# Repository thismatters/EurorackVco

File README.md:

# Voltage Controlled Oscillator

A Voltage Contolled Oscillator (VCO) is the backbone module for subtractive synthesis. It generates an audio signal which can then be shaped by myriad filters and amplifiers. Without a VCO you don't have a synth.

The circuit here is based on the [Yusynth VCO](https://yusynth.net/Modular/EN/VCO/index.html) with minor tweaks to make it more Eurorack friendly. The changes I've made are thus:
* Selected resistors appropriate for +/-12V rails,
* Added polarity protection so that a backward power header doesn't fry anything (twin series schotty diodes: BAT54SL),
* Selected a modern dual NPN diode package for the exponential converter,
* Full surface mount design,
* Toggle switch on front face for sync hardness.

The Yusynth page is a treasure trove of information about this circuit that I am too amateur to claim as my own; please read that outstanding page before using this circuit. The page provides several other implementations of the circuit that you may find suitable.

The KiCAD project here uses the library/footprints [found in my companion repo](https://github.com/thismatters/EurorackKiCAD).

## Width

10hp on a standard 3U rack.

## Inputs

This VCO features dual inputs for 1V/oct, Linear FM, and Exponential FM, Sync, and PWM. A toggle switch on the front face allows the player to set sync hardness. Two potentiometers allow the setting of frequency offset: coarse and fine. Two potentiometers are devoted to level for each of the frequency modulators (linear and exponential). Another pair of potentiometers gives control over (inherent) pulse width and PWM input level.

## Outputs

Four wave shapes are simultaneously available:
* Sine
* Triangle
* Saw (falling)
* Square

## Fiddly bits

Three 100kOhm resistors (R3, R4, R5) should be selected to within 0.1% tolerance (of each other) for good input tracking.

Likewise, two diodes (D5 and D6) ought to be selected which have a closely matched bias voltage in order to ensure a good sine wave symmetry. Testing SMD diodes for bias voltage is no small feat, so I didn't really bother doing this on my test circuits and first printed boards and they seemed fine. I hasten to bet that manufacturing processes have improved to the extent that manual matching is no longer relevant; but that could also just be a justification for laziness!

The schematic shows an OPA2134, however the original circuit calls for an OPA2137. The OPA2134 is a higher quality chip for sound applications, but it is also more expensive and was out of stock when I went to order; the OPA2137 is a suitable alternative.

The schematic calls for a `thermally_coupled_transistor_pair`; this is actually two components arranged carefully together. First a dual NPN transistor array (BCM847), then a thermco resistor which is nestled directly atop the transistor array package and the couple are blanketed in thermal grease so that the two components stay close to the same temperature.

## Adjustment

You'll need an oscilloscope, a CV keyboard, and ideally a tuner.

### Waveshape

1. Set the frequency potentiometers to their middle positions, set the FM and PWM level knobs to minimum (counterclockwise), and the PW knob to the middle position.
1. Connect the sawtooth output to the oscilloscope.
1. Power on the circuit.
1. Adjust RV10 until the sawtooth fills the full covers 10V from peak to peak (no horizontal line at top or bottom).
1. Adjust RV9 until the sawtooth is centered about 0V. (You may have to revisit RV10 to get this perfect; before moving on the saw wave should fill the +/-5V range)
1. Connect the triangle output to the oscilloscope.
1. Adjust RV9 some more to get the triangle shape just right.
1. Adjust RV11 until the triangle is centered around 0V. (You may have to revisit RV10 to get this perfect)
1. Connect the sine output to the oscilloscope.
1. The sine wave ought to look about right, but you may adjust RV9, RV11 (and possibly RV10) to hone this.

### Volt/Octave Tracking

1. Connect the CV source to the 1V/oct input, set the CV to 0V. If you're using a keyboard for this, hit C0.
1. Connect your tuner to the sine output.
1. Set CV to 0V, adjust the frequency knobs (coarse, then fine) until the tuner shows A1* (55Hz), then set the CV to 1V (press C1).
1. If the tuner shows A2 (110Hz) then you're all set, move on to the next step. Otherwise, if the pitch is sharp (>110Hz) adjust RV8 so that the pitch goes sharper (if flat go flatter)! Now go back to the prior step.
1. Repeat the prior _two_ steps this time jumping an additional octave. Once you've worked through all the octaves you have available then you're done!

| Tone | Frequency |
|------|-----------|
| A1   |   55 Hz   |
| A2   |   110 Hz  |
| A3   |   220 Hz  |
| A4   |   440 Hz  |
| A5   |   880 Hz  |
| A6   |   1760 Hz |
| A7   |   3520 Hz |
| A8   |   7040 Hz |

\* A1 was chosen because it has a nice round number for a frequency which makes it easy to dial in on an oscilloscope. If you have a tuner use whatever pitch you like.

### Tuning

1. Disconnect all inputs from circuit.
1. Connect the tuner to the sine output.
1. Set the coarse frequency knob to the fully counterclockwise position (0), set the fine frequency knob to the middle position (0).
1. Connect a CV keyboard to the 1v/oct input, then press A3 (220Hz).
1. Adjust RV6 until the frequency is 220Hz.

## Vendors

There are part numbers in the [BOM](vco.csv) for many of the parts (not for basic passives though) at the following vendors:

* [Mouser](https://www.mouser.com): Needs no introduction. Get your ICs from here (or [digikey](https://www.digikey.com)).
* [Tayda Electronics](https://www.taydaelectronics.com/): Good supplier for passive components; audio jacks, and potentiometers. Their audio jacks are slightly smaller than the thonkiconn from thonk.
* [Thonk](https://www.thonk.co.uk/): The only place I've found tempco resistors for sale! You're looking for the 1k resistor, their store doesn't support part number searches. These are apparently sold out forever and no longer manufactured... I'll look around for alternatives, and experiment with omitting that resistor...
* [Love My Switches](https://lovemyswitches.com/): Has [really good knobs](https://lovemyswitches.com/anodized-aluminum-knob-the-lo-fi-1-4-smooth-shaft-12-5mm-od/) to go on those potentiometers!
* [OSHPark](https://oshpark.com/): Fast and (relatively) cheap PCB manufacturer. [The V1 circuit](https://oshpark.com/shared_projects/FmhO6zEO) works great, but you may have a hard time finding the 1K thermco resistor.

## Changelog

### v1
- first draft

### v2
- Added polarity protection,
- bigger holes for toggle switch footprint,
- reorganized board for easier trace routing,
- updated design language,
- narrowed by 2hp,
- changed some resistor values for more consistent +/-5V output,

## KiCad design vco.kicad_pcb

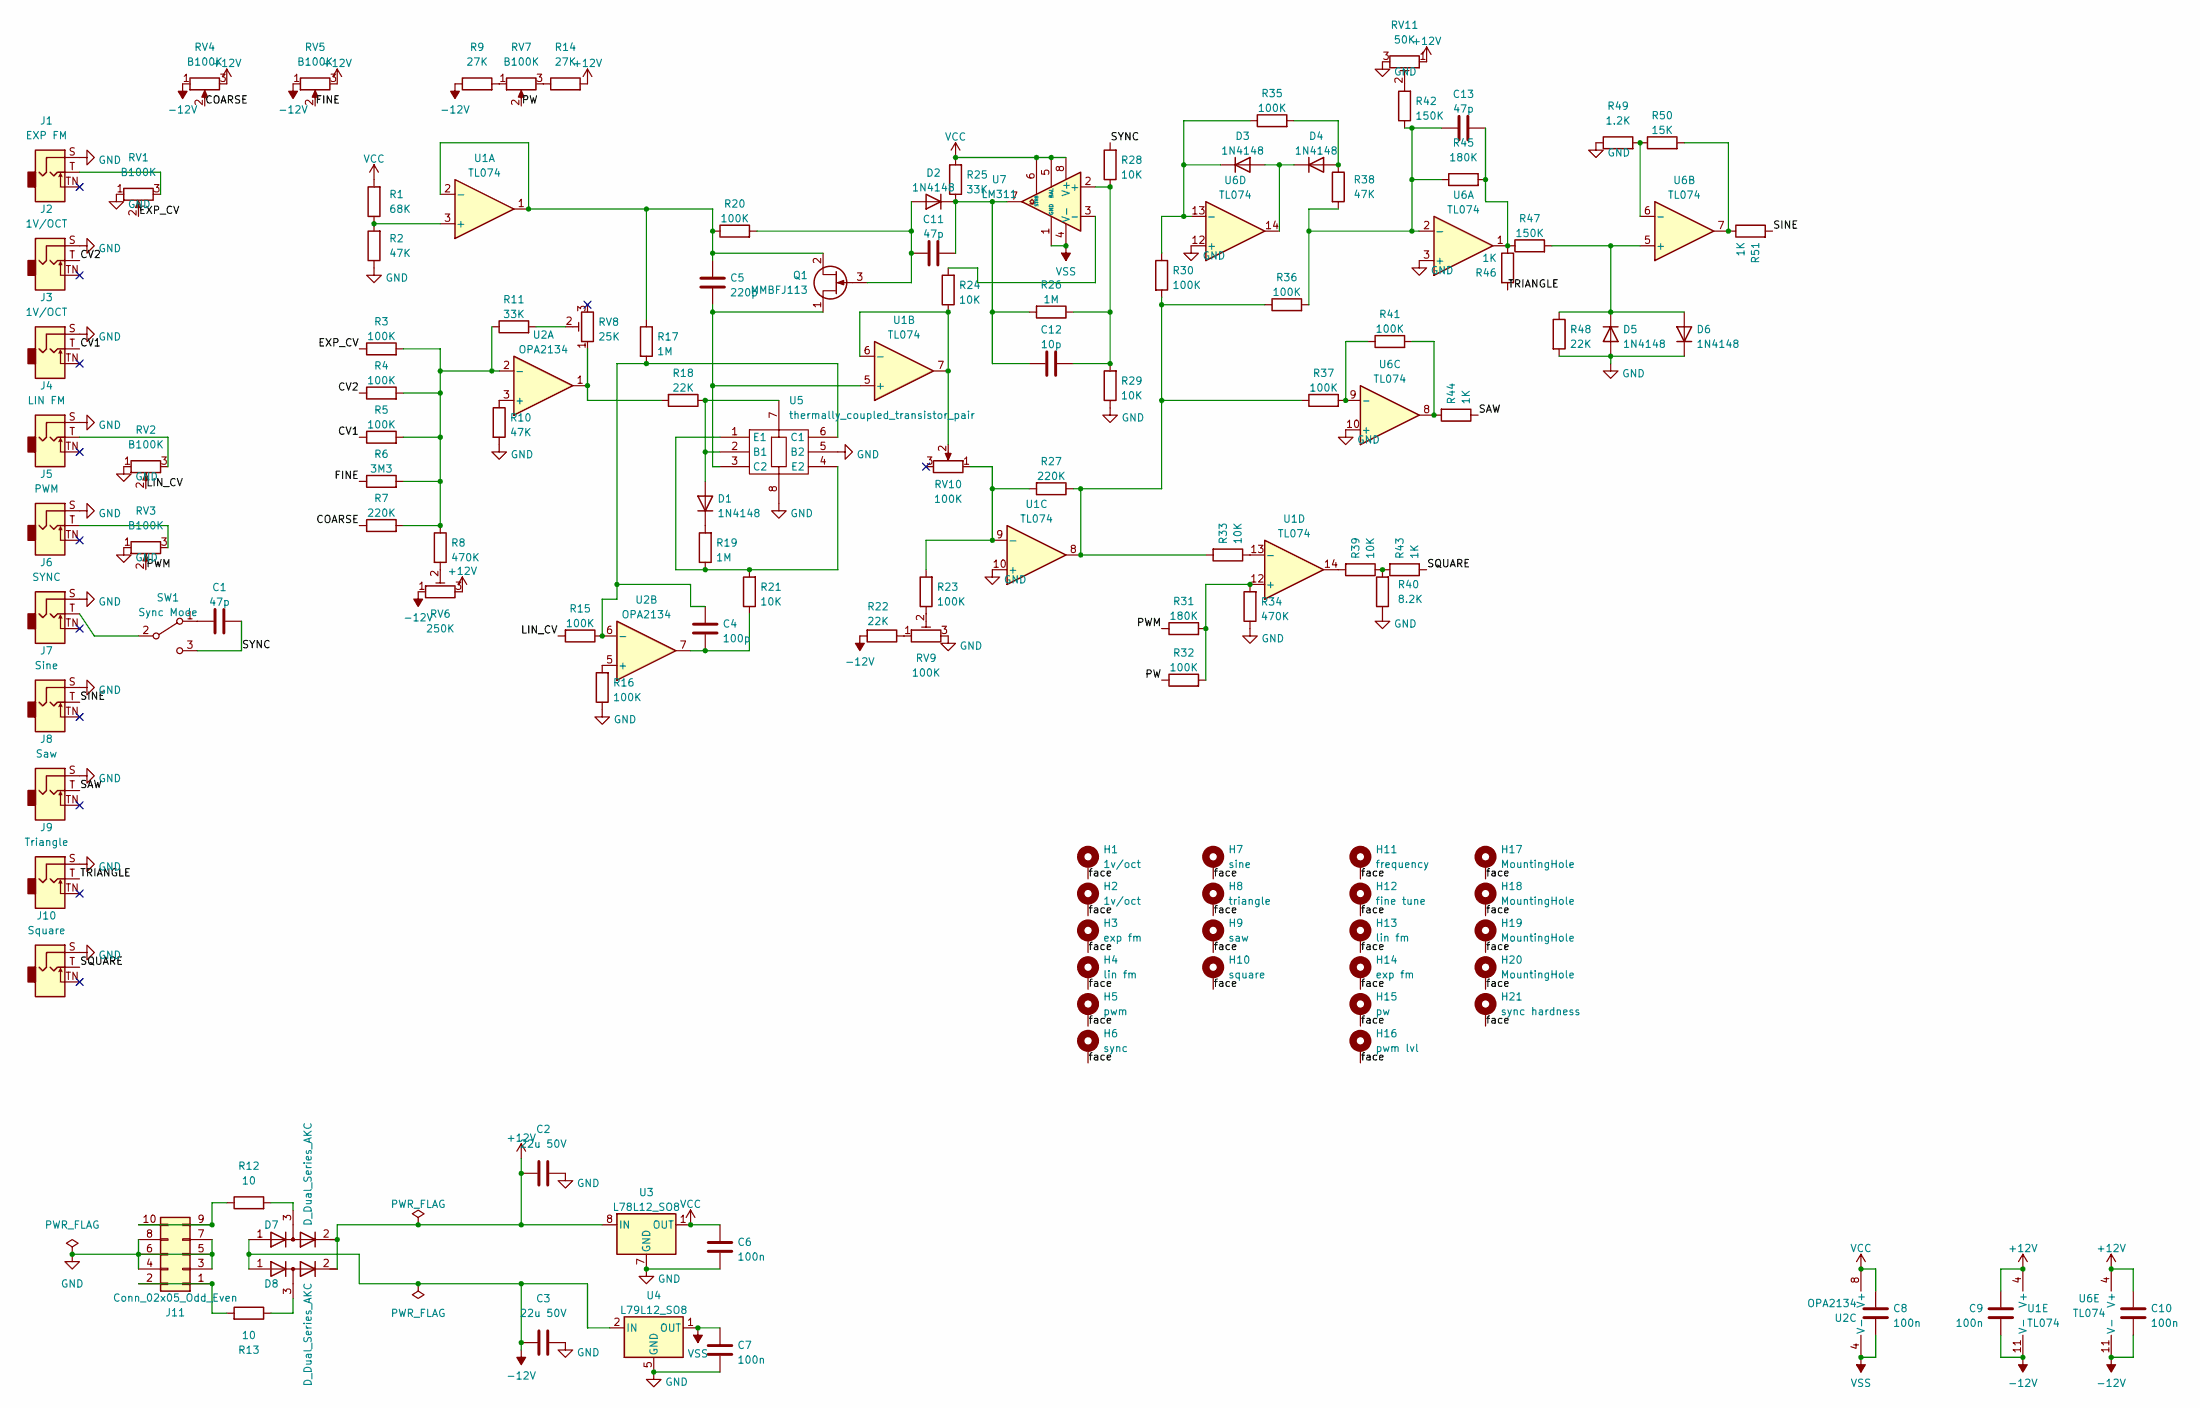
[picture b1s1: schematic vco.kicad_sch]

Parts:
C1, C11, C13: 47p; C_0805_2012Metric
C2, C3: 22u 50V; CP_Radial_D5.0mm_P2.50mm
C4: 100p; C_0805_2012Metric
C5: 220p; C_0805_2012Metric
C6, C7, C8, C9, C10: 100n; C_0805_2012Metric
C12: 10p; C_0805_2012Metric
D1, D2, D3, D4, D5, D6: 1N4148; D_SOD-323_HandSoldering
D7, D8: D_Dual_Series_AKC; SOT-23; PartNum 863-BAT54SLT1G
H1, H2: 1v/oct; Mech-AudioJack-Hole-Input-Voct
H3: exp fm; Mech-AudioJack-Hole-Input-CV
H4: lin fm; Mech-AudioJack-Hole-Input-CV
H5: pwm; Mech-AudioJack-Hole-Input-CV
H6: sync; Mech-AudioJack-Hole-Input-Clock
H7: sine; Mech-AudioJack-Hole-Output
H8: triangle; Mech-AudioJack-Hole-Output
H9: saw; Mech-AudioJack-Hole-Output
H10: square; Mech-AudioJack-Hole-Output
H11: frequency; Mech-Potentiometer-Hole_level
H12: fine tune; Mech-Potentiometer-Hole_pan
H13: lin fm; Mech-Potentiometer-Hole_level
H14: exp fm; Mech-Potentiometer-Hole_level
H15: pw; Mech-Potentiometer-Hole_pan
H16: pwm lvl; Mech-Potentiometer-Hole_level
H17, H18, H19, H20: MountingHole; Mech-MountingHole
H21: sync hardness; Mech-2M_Switch-Hole
J1: EXP FM; AudioJack2_Tayda_A-2566; PartNum A-2566
J2, J3: 1V/OCT; AudioJack2_Tayda_A-2566; PartNum A-2566
J4: LIN FM; AudioJack2_Tayda_A-2566; PartNum A-2566
J5: PWM; AudioJack2_Tayda_A-2566; PartNum A-2566
J6: SYNC; AudioJack2_Tayda_A-2566; PartNum A-2566
J7: Sine; AudioJack2_Tayda_A-2566; PartNum A-2566
J8: Saw; AudioJack2_Tayda_A-2566; PartNum A-2566
J9: Triangle; AudioJack2_Tayda_A-2566; PartNum A-2566
J10: Square; AudioJack2_Tayda_A-2566; PartNum A-2566
J11: Conn_02x05_Odd_Even; PinHeader_2x05_P2.54mm_Vertical; PartNum A-2939
Q1: MMBFJ113; SOT-23; PartNum 512-MMBFJ113
R1: 68K; R_0805_2012Metric
R2, R10, R38: 47K; R_0805_2012Metric
R3, R4, R5, R15, R16, R20, R23, R30, R32, R35, R36, R37, R41: 100K; R_0805_2012Metric
R6: 3M3; R_0805_2012Metric
R7, R27: 220K; R_0805_2012Metric
R8, R34: 470K; R_0805_2012Metric
R9, R14: 27K; R_0805_2012Metric
R11, R25: 33K; R_0805_2012Metric
R12, R13: 10; R_0805_2012Metric
R17, R19, R26: 1M; R_0805_2012Metric
R18, R22, R48: 22K; R_0805_2012Metric
R21, R24, R28, R29, R33, R39: 10K; R_0805_2012Metric
R31, R45: 180K; R_0805_2012Metric
R40: 8.2K; R_0805_2012Metric
R42, R47: 150K; R_0805_2012Metric
R43, R44, R46, R51: 1K; R_0805_2012Metric
R49: 1.2K; R_0805_2012Metric
R50: 15K; R_0805_2012Metric
RV1, RV2, RV3, RV4, RV5, RV7: B100K; Potentiometer_RV16AF-41-15R1; PartNum A-2963
RV6: 250K; Potentiometer_Bourns_3296W_Vertical; PartNum A-310
RV8: 25K; Potentiometer_Bourns_3296W_Vertical; PartNum A-595
RV9: 100K; Potentiometer_Bourns_3296W_Vertical
RV10: 100K; Potentiometer_Bourns_3296W_Vertical; PartNum A-587
RV11: 50K; Potentiometer_Bourns_3296W_Vertical; PartNum A-598
SW1: Sync Mode; Switch_SPDT_Tayda_A-5751; PartNum A-5751
U1, U6: TL074; SOIC-14_3.9x8.7mm_P1.27mm; PartNum 595-TL074CDR
U2: OPA2134; SO-8_3.9x4.9mm_P1.27mm; PartNum 595-OPA2134UA/2K5
U3: L78L12_SO8; SOIC-8_3.9x4.9mm_P1.27mm; PartNum 863-NCV78L12ABDR2G
U4: L79L12_SO8; SOIC-8_3.9x4.9mm_P1.27mm; PartNum 863-MC79L12ABDR2G
U5: thermally_coupled_transistor_pair; SOT457+thermco_resistor; PartNum 771-BCM847DS135 --and-- LT16S102F33
U7: LM311; SOIC-8_3.9x4.9mm_P1.27mm; PartNum 863-LM311DR2G

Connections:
+12V: C2.1, C9.1, C10.1, D7.2 (K), D8.2 (K), R14.2, RV4.3, RV5.3, RV6.3, RV11.1, U1.4 (V+), U3.8 (IN), U6.4 (V+)
-12V: C3.1, C9.2, C10.2, D7.1 (A), D8.1 (A), R9.1, R22.2, RV4.1, RV5.1, RV6.1, U1.11 (V-), U4.2 (IN), U4.3 (IN), U4.6 (IN), U4.7 (IN), U6.11 (V-)
/COARSE: R7.1, RV4.2
/CV1: J3.T, R5.1
/CV2: J2.T, R4.1
/EXP_CV: R3.1, RV1.2
/FINE: R6.1, RV5.2
/LIN_CV: R15.2, RV2.2
/PW: R32.1, RV7.2
/PWM: R31.1, RV3.2
/SAW: J8.T, R44.1
/SINE: J7.T, R51.2
/SQUARE: J10.T, R43.1
/SYNC: C1.1, R28.2, SW1.3 (C)
/TRIANGLE: J9.T, R46.2
/face: H1.1, H2.1, H3.1, H4.1, H5.1, H6.1, H7.1, H8.1, H9.1, H10.1, H11.1, H12.1, H13.1, H14.1, H15.1, H16.1, H17.1, H18.1, H19.1, H20.1, H21.1
GND: C2.2, C3.2, C6.2, C7.2, D5.2 (A), D6.1 (K), J1.S, J2.S, J3.S, J4.S, J5.S, J6.S, J7.S, J8.S, J9.S, J10.S, J11.3, J11.4, J11.5, J11.6, J11.7, J11.8, R2.1, R10.2, R16.1, R29.1, R34.1, R40.1, R48.2, R49.1, RV1.1, RV2.1, RV3.1, RV9.3, RV11.3, U1.10 (+), U3.2 (GND), U3.3 (GND), U3.6 (GND), U3.7 (GND), U4.5 (GND), U5.5 (B2), U5.8, U6.3 (+), U6.10 (+), U6.12 (+)
unnamed: C4.1, R21.1, U2.7
unnamed: C13.1, R45.2, R46.1, R47.1, U6.1
unnamed: D1.2 (A), R18.1, U5.2 (B1), U5.7
unnamed: D1.1 (K), R19.2
unnamed: C11.2, D2.2 (A), Q1.3 (G), R20.2
unnamed: C11.1, C12.2, D2.1 (K), R25.1, R26.2, U7.7
unnamed: D3.2 (A), D4.1 (K), U6.14
unnamed: D3.1 (K), R30.1, R35.1, U6.13 (-)
unnamed: D4.2 (A), R35.2, R38.1
unnamed: D5.1 (K), D6.2 (A), R47.2, R48.1, U6.5 (+)
unnamed: D7.3 (common), R12.2
unnamed: D8.3 (common), R13.1
unnamed: J1.T, RV1.3
unnamed: J4.T, RV2.3
unnamed: J5.T, RV3.3
unnamed: J11.1, J11.2, R13.2
unnamed: J11.9, J11.10, R12.1
unnamed: C5.1, Q1.1 (D), U1.5 (+), U5.3 (C2)
unnamed: C5.2, Q1.2 (S), R17.1, R20.1, U1.1, U1.2 (-)
unnamed: R8.2, RV6.2
unnamed: R9.2, RV7.1
unnamed: R11.2, RV8.2
unnamed: R14.1, RV7.3
unnamed: R18.2, RV8.1, U2.1
unnamed: R22.1, RV9.1
unnamed: R23.1, RV9.2
unnamed: R27.1, R30.2, R33.2, R36.1, R37.1, U1.8
unnamed: R39.1, R40.2, R43.2
unnamed: R39.2, U1.14
unnamed: R41.2, R44.2, U6.8
unnamed: R42.2, RV11.2
unnamed: R50.2, R51.1, U6.7
unnamed: C1.2, SW1.1 (A)
unnamed: J6.T, SW1.2 (B)
unnamed: R1.1, R2.2, U1.3 (+)
unnamed: R24.1, RV10.2, U1.6 (-), U1.7
unnamed: R23.2, R27.2, RV10.1, U1.9 (-)
unnamed: R31.2, R32.2, R34.2, U1.12 (+)
unnamed: R33.1, U1.13 (-)
unnamed: R10.1, U2.3 (+)
unnamed: R3.2, R4.2, R5.2, R6.2, R7.2, R8.1, R11.1, U2.2 (-)
unnamed: R16.2, U2.5 (+)
unnamed: C4.2, R15.1, R17.2, U2.6 (-), U5.6 (C1)
unnamed: R19.1, R21.2, U5.1 (E1), U5.4 (E2)
unnamed: C13.2, R36.2, R38.2, R42.1, R45.1, U6.2 (-)
unnamed: R49.2, R50.1, U6.6 (-)
unnamed: R37.2, R41.1, U6.9 (-)
unnamed: C12.1, R26.1, R28.1, R29.2, U7.2 (+)
unnamed: R24.2, U7.3 (-)
VCC: C6.1, C8.1, R1.2, R25.2, U2.8 (V+), U3.1 (OUT), U7.5 (BAL), U7.6 (STRB), U7.8 (V+)
VSS: C7.1, C8.2, U2.4 (V-), U4.1 (OUT), U7.1 (GND), U7.4 (V-)

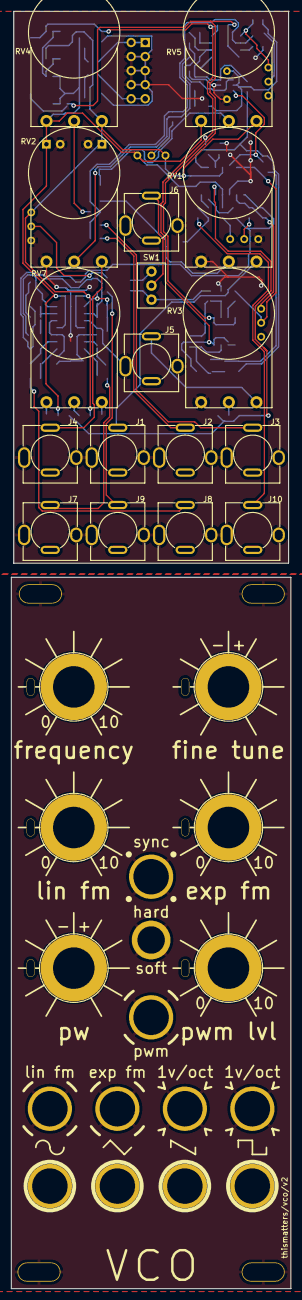
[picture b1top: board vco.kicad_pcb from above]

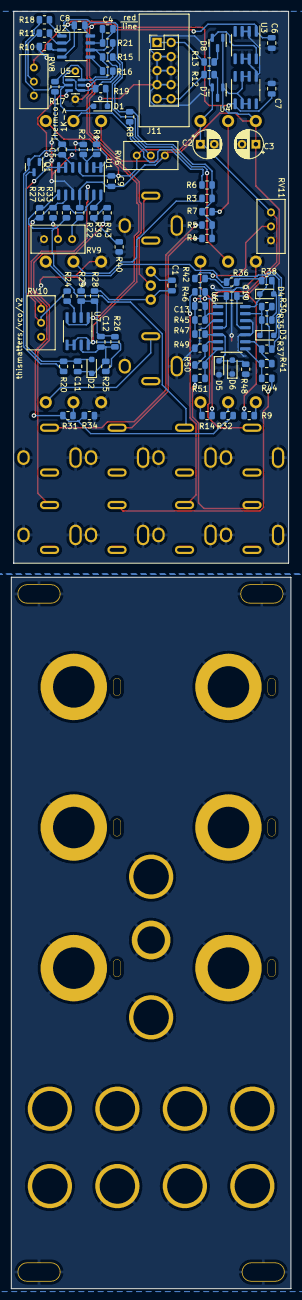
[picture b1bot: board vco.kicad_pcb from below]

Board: 2 copper layers, 50.5 x 230.7 mm, 124 parts (86 on the bottom side), 68 nets.

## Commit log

2023-02-15 checking all resistor values
2024-01-02 v2 ready for manu
2024-01-02 wrong part number
2024-01-14 small readme change
2024-12-27 v2 just about ready for manu
2024-12-27 bom fixes
2024-12-27 more bom fixes
2024-12-27 use bigger potentiometers (i've got some)
2024-12-27 one last resistor value
2024-12-27 trimmer values
2025-01-11 pcb updated for v2
2025-03-29 v2 built
